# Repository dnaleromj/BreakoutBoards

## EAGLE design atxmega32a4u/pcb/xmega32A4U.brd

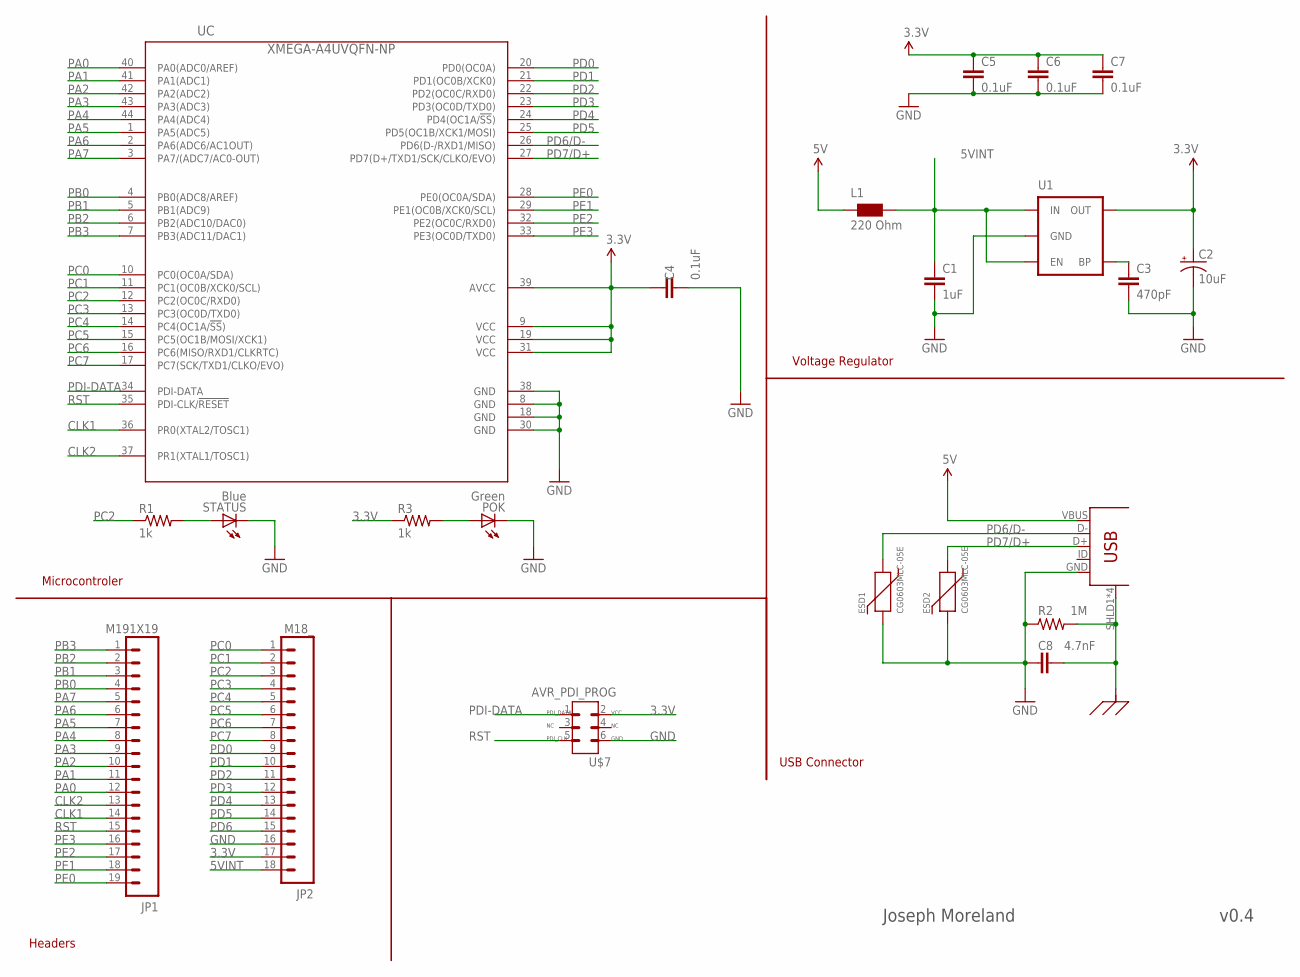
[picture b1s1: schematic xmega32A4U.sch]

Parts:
C1: 1uF; 0603-CAP; PARTNO C0603C105K3PACTU
C2: 10uF; EIA3216; PARTNO T494A106M020AT
C3: 470pF; 0603-CAP; PARTNO C0603C471K5RACTU
C4, C5, C6, C7: 0.1uF; 0402-CAP; PARTNO GMK105BJ104KV-F
C8: 4.7nF; 0402-CAP; PARTNO C0402C472K3RACTU
ESD1, ESD2: CG0603MLC-05E; 0603-CHIPGUARD; PARTNO CG0603MLC-05E
JP1: M191X19; 1X19; PARTNO M20-9732046
JP2: M18_; 1X18; PARTNO 68000-418HLF
L1: 220 Ohm; 0603; PARTNO MPZ1608S221A
POK: Green; LED-0603; PARTNO LTST-C190KGKT
R1, R3: 1k; 0603-RES; PARTNO RC0603FR-071KL
R2: 1M; 0402-RES; PARTNO CRCW04021M00JNED
STATUS: Blue; LED-0603; PARTNO LTST-C191TBKT
U1: V_REG_MIC52193.3V; SOT23-5; PARTNO MIC5219-3.3YM5 TR
U$4: USB-MINIB; USB-MINI-B-UX60-MB-5S8; PARTNO UX60-MB-5S8
U$7: AVR_PDI_PROG; AVR_50MIL_PROG; PARTNO LPPB032NFSP-RC
UC: XMEGA-A4UVQFN-NP; QFN44-NOPAD; PARTNO ATXMEGA32A4U-MH

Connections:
3.3V: C2.A (+), C4.1, C5.1, C6.1, C7.1, JP2.17, R3.1, U1.5 (OUT), U$7.2 (VCC), UC.9 (VCC), UC.19 (VCC), UC.31 (VCC), UC.39 (AVCC)
5V: L1.1, U$4.VBUS
5VINT: C1.1, JP2.18, L1.2, U1.1 (IN), U1.3 (EN)
CLK1: JP1.14, UC.36 (PR0(XTAL2/TOSC1))
CLK2: JP1.13, UC.37 (PR1(XTAL1/TOSC1))
GND: C1.2, C2.C (-), C3.2, C4.2, C5.2, C6.2, C7.2, C8.1, ESD1.P$1, ESD2.P$1, JP2.16, POK.C, R2.1, STATUS.C, U1.2 (GND), U$4.GND, U$7.6 (GND), UC.8 (GND), UC.18 (GND), UC.30 (GND), UC.38 (GND)
unnamed: POK.A, R3.2
unnamed: R1.2, STATUS.A
unnamed: C3.1, U1.4 (BP)
PA0: JP1.12, UC.40 (PA0(ADC0/AREF))
PA1: JP1.11, UC.41 (PA1(ADC1))
PA2: JP1.10, UC.42 (PA2(ADC2))
PA3: JP1.9, UC.43 (PA3(ADC3))
PA4: JP1.8, UC.44 (PA4(ADC4))
PA5: JP1.7, UC.1 (PA5(ADC5))
PA6: JP1.6, UC.2 (PA6(ADC6/AC1OUT))
PA7: JP1.5, UC.3 (PA7/(ADC7/AC0-OUT))
PB0: JP1.4, UC.4 (PB0(ADC8/AREF))
PB1: JP1.3, UC.5 (PB1(ADC9))
PB2: JP1.2, UC.6 (PB2(ADC10/DAC0))
PB3: JP1.1, UC.7 (PB3(ADC11/DAC1))
PC0: JP2.1, UC.10 (PC0(OC0A/SDA))
PC1: JP2.2, UC.11 (PC1(OC0B/XCK0/SCL))
PC2: JP2.3, R1.1, UC.12 (PC2(OC0C/RXD0))
PC3: JP2.4, UC.13 (PC3(OC0D/TXD0))
PC4: JP2.5, UC.14 (PC4(OC1A/!SS!))
PC5: JP2.6, UC.15 (PC5(OC1B/MOSI/XCK1))
PC6: JP2.7, UC.16 (PC6(MISO/RXD1/CLKRTC))
PC7: JP2.8, UC.17 (PC7(SCK/TXD1/CLKO/EVO))
PD0: JP2.9, UC.20 (PD0(OC0A))
PD1: JP2.10, UC.21 (PD1(OC0B/XCK0))
PD2: JP2.11, UC.22 (PD2(OC0C/RXD0))
PD3: JP2.12, UC.23 (PD3(OC0D/TXD0))
PD4: JP2.13, UC.24 (PD4(OC1A/!SS!))
PD5: JP2.14, UC.25 (PD5(OC1B/XCK1/MOSI))
PD6: JP2.15
PD6/D-: ESD1.P$2, U$4.D-, UC.26 (PD6(D-/RXD1/MISO))
PD7/D+: ESD2.P$2, U$4.D+, UC.27 (PD7(D+/TXD1/SCK/CLKO/EVO))
PDI-DATA: U$7.1 (PDI_DATA), UC.34 (PDI-DATA)
PE0: JP1.19, UC.28 (PE0(OC0A/SDA))
PE1: JP1.18, UC.29 (PE1(OC0B/XCK0/SCL))
PE2: JP1.17, UC.32 (PE2(OC0C/RXD0))
PE3: JP1.16, UC.33 (PE3(OC0D/TXD0))
RST: JP1.15, U$7.5 (PDI_CLK), UC.35 (PDI-CLK/!RESET)
SHLD: C8.2, R2.2, U$4.SHLD1 (SHLD), U$4.SHLD2 (SHLD), U$4.SHLD3 (SHLD), U$4.SHLD4 (SHLD)

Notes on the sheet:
Headers
Voltage Regulator
Microcontroler
USB Connector
Joseph Moreland
v0.4

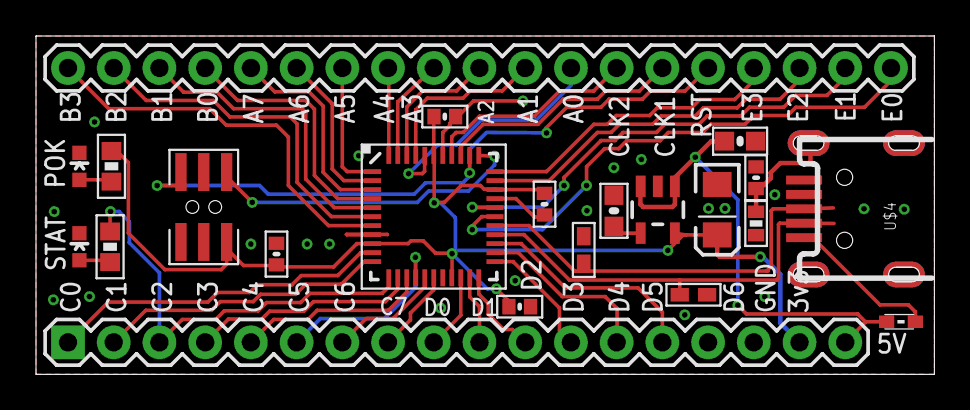
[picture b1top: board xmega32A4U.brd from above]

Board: 2 copper layers, 49.9 x 18.8 mm, 23 parts (1 on the bottom side), 44 nets.

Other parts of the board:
U$6: OSHW-LOGO-S

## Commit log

2013-04-28 Label cleanup on pins. Moved from PA1 style name to A1 to save space.
2013-05-05 Fix ciruit errors in LDO, added ESD protection to USB circuit - this will be v0.3
    v0.3 ready
2013-05-05 BOM corrected and updated for 1k and 1M resistors
2013-05-14 V1.4 production scripts set, boards sent to Seeed and Smart Prototyping
2014-05-03 CY8C4245LQI breakout added
2014-05-04 master workspace set up

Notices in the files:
parts and their libraries:
SparkFun-PowerIC: Licensing: CC v3.0 Share-Alike You are welcome to use this library for commercial purposes.
